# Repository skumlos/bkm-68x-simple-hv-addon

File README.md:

BKM-68X Alternative HV Sync Add-on

This small experimental board is meant to wired to the BKM-68X Alternative Rev. E1 (or earlier that has the HD_SD_X pad) to
provide a discrete VSYNC input, and thus support RGBHV signals. The FPGA needs to be programmed with at least version 1.3 of
the firmware, and using the Quartus project where the HD_SD_X pin has been reconfigured to discrete VSYNC in.

Since the board cannot easily be soldered and fastened to the BKM-68X Alternative board, it is meant to be fastened to the
bracket, so the bracket needs to be replaced with bracket that has the appropriate hole. The Keystone 7794 is not mandatory
but will provide further support of the board if used. The BNC jack needs to be rather low profile to avoid the THT pins
touching the board, seemingly the Molex 73171-0702 is appropriate.

The board needs 5 connections, two going to the "analog part" of the board, that being the 5V and GNDA, two going to the
"digital part" being 3.3V and GND. FPGA SYNC pad then needs to be wired to the HD_SD_X pad. As the VSYNC signal is rather
low speed (so 50/60Hz) routing/wiring shouldn't be extremely important, but try to keep the wire close to the "digital"
ground part. C103 is as such optional, if chosen it should most likely be in the 1nF range. It is there to help the return
path of the signals.

Use at your own risk, very untested :)

(2022) Martin Hejnfelt (martin@hejnfelt.com)
www.immerhax.com

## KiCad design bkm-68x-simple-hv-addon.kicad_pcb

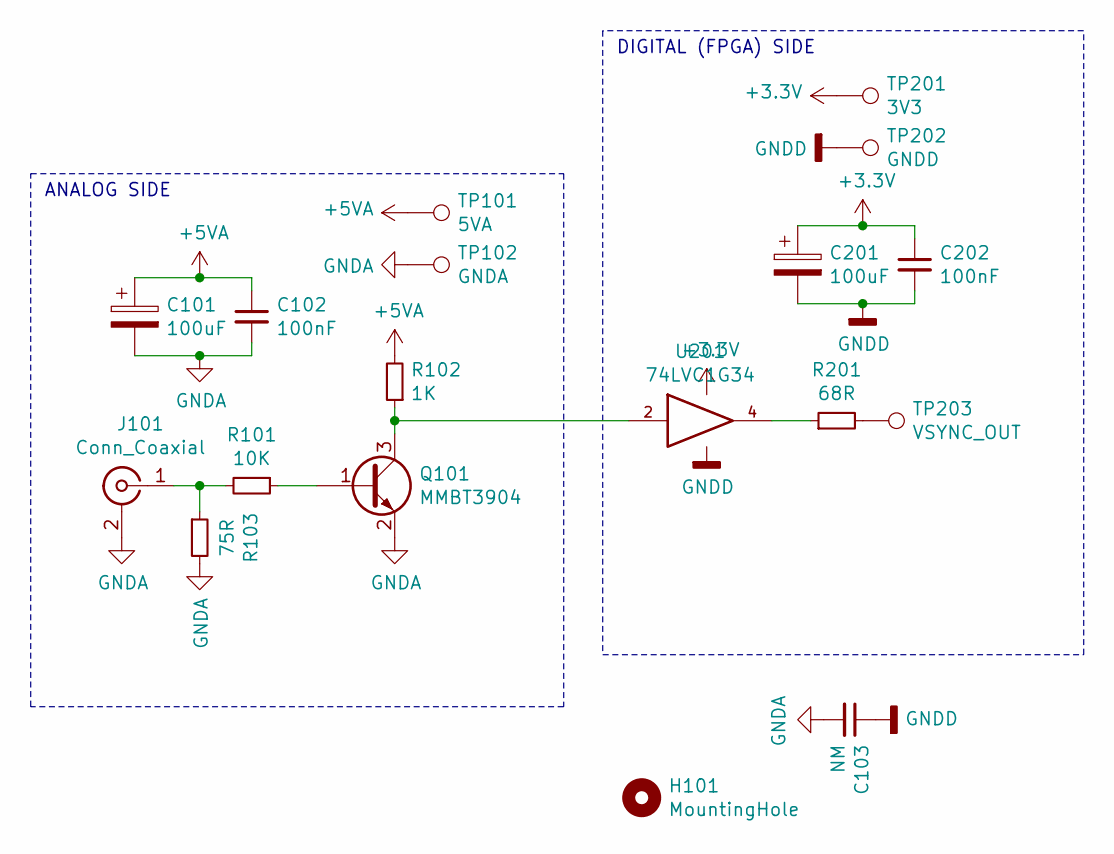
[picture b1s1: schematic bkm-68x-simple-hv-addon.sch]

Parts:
C101, C201: 100uF; CP_Elec_6.3x5.4; JLC SMD,6.3x5.5mm
C102, C202: 100nF; C_0805_2012Metric_Pad1.18x1.45mm_HandSolder; JLC 0805
C103: NM; C_0805_2012Metric_Pad1.18x1.45mm_HandSolder; JLC 0805
H101: MountingHole; 7794-X
J101: Conn_Coaxial; BNC-THT
Q101: MMBT3904; SOT-23; JLC SOT-23(SOT-23-3)
R101: 10K; R_0805_2012Metric_Pad1.20x1.40mm_HandSolder; JLC 0805
R102: 1K; R_0805_2012Metric_Pad1.20x1.40mm_HandSolder; JLC 0805
R103: 75R; R_0805_2012Metric_Pad1.20x1.40mm_HandSolder; JLC 0805
R201: 68R; R_0805_2012Metric_Pad1.20x1.40mm_HandSolder; JLC 0805
TP101: 5VA; TestPoint_Pad_2.5x2.5mm
TP102: GNDA; TestPoint_Pad_2.5x2.5mm
TP201: 3V3; TestPoint_Pad_2.5x2.5mm
TP202: GNDD; TestPoint_Pad_2.5x2.5mm
TP203: VSYNC_OUT; TestPoint_Pad_2.5x2.5mm
U201: 74LVC1G34; SOT-23-5_HandSoldering; JLC SOT-23-5

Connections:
+3V3: C201.1, C202.1, TP201.1, U201.5 (VCC)
+5VA: C101.1, C102.1, R102.2, TP101.1
GND: C103.1, C201.2, C202.2, TP202.1, U201.3 (GND)
GNDA: C101.2, C102.2, C103.2, J101.2 (Ext), Q101.2 (E), R103.2, TP102.1
unnamed: J101.1 (In), R101.2, R103.1
unnamed: Q101.1 (B), R101.1
unnamed: Q101.3 (C), R102.1, U201.2
unnamed: R201.1, U201.4
unnamed: R201.2, TP203.1

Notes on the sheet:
ANALOG SIDE
DIGITAL (FPGA) SIDE

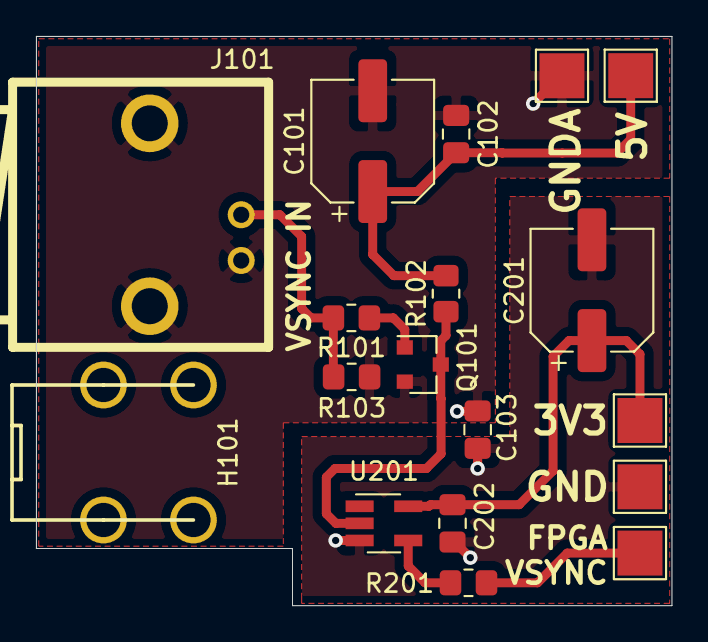
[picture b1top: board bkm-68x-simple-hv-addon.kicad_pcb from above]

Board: 2 copper layers, 35.3 x 31.6 mm, 18 parts (0 on the bottom side), 9 nets.

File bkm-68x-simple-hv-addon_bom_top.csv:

"Comment","Designator","Footprint","LCSC Part #"
"Conn_Coaxial","J101","",""
"10K","R101","0805","C84376"
"1K","R102","0805","C95781"
"75R","R103","0805","C141697"
"MMBT3904","Q101","SOT-23(SOT-23-3)","C94514"
"68R","R201","0805","C137498"
"100uF","C101 C201","SMD,6.3x5.5mm","C111600"
"100nF","C102 C202","0805","C1711"
"NM","C103","0805",""
"74LVC1G34","U201","SOT-23-5","C840096"

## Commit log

2022-06-17 Initial Rev. A
2022-06-17 Add README
